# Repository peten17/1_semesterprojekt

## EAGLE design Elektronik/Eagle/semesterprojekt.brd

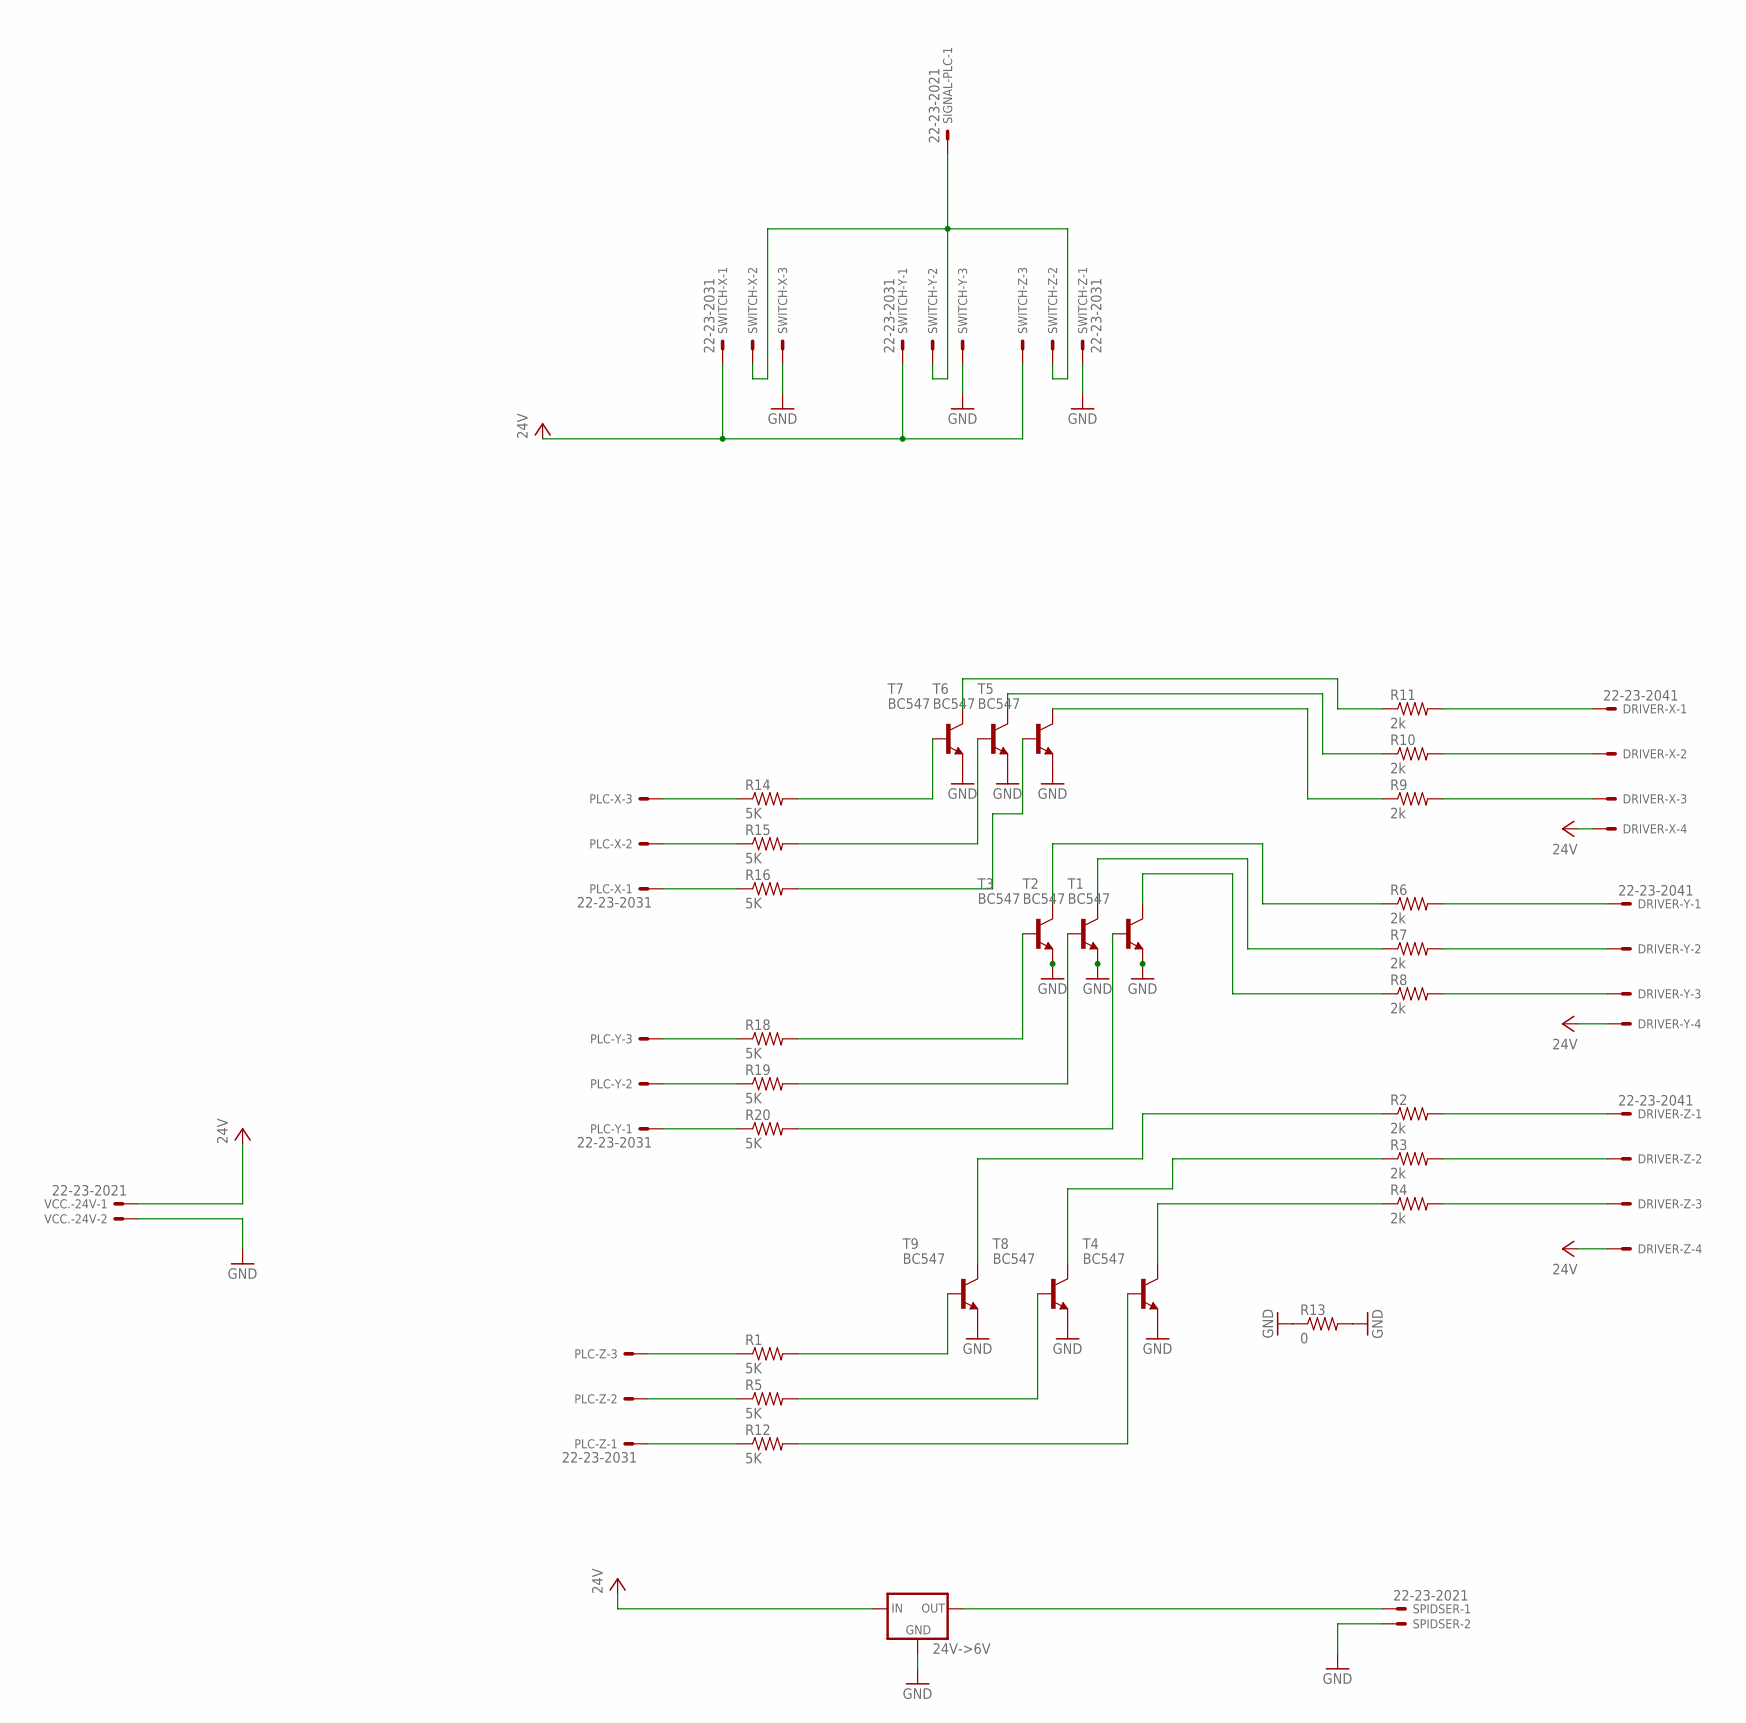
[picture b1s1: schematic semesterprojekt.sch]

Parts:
24V->6V: 78XXS
DRIVER-X: 22-23-2041
DRIVER-Y: 22-23-2041
DRIVER-Z: 22-23-2041
PLC-X: 22-23-2031
PLC-Y: 22-23-2031
PLC-Z: 22-23-2031
R1, R5, R12, R14, R15, R16, R18, R19, R20: 5K; 0204/7
R2, R3, R4, R6, R7, R8, R9, R10, R11: 2k; 0204/7
R13: 0; 0204/7
SIGNAL-PLC: 22-23-2021
SPIDSER: 22-23-2021
SWITCH-X: 22-23-2031
SWITCH-Y: 22-23-2031
SWITCH-Z: 22-23-2031
T1, T2, T3, T4, T5, T6, T7, T8, T9: BC547; TO92
VCC.-24V: 22-23-2021

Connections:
GND: 24V->6V.GND, R13.1, R13.2, SPIDSER.2, SWITCH-X.3, SWITCH-Y.3, SWITCH-Z.1, T1.3 (E), T2.3 (E), T3.3 (E), T4.3 (E), T5.3 (E), T6.3 (E), T7.3 (E), T8.3 (E), T9.3 (E), VCC.-24V.2
unnamed: DRIVER-Z.1, R2.2
unnamed: DRIVER-Z.2, R3.2
unnamed: DRIVER-Z.3, R4.2
unnamed: 24V->6V.OUT, SPIDSER.1
unnamed: R14.2, T7.2 (B)
unnamed: R15.2, T6.2 (B)
unnamed: R16.2, T5.2 (B)
unnamed: PLC-X.2, R15.1
unnamed: R18.2, T3.2 (B)
unnamed: R19.2, T2.2 (B)
unnamed: R20.2, T1.2 (B)
unnamed: R4.1, T4.1 (C)
unnamed: PLC-X.1, R16.1
unnamed: SIGNAL-PLC.1, SWITCH-X.2, SWITCH-Y.2, SWITCH-Z.2
unnamed: PLC-Y.3, R18.1
unnamed: R8.1, T1.1 (C)
unnamed: DRIVER-Y.3, R8.2
unnamed: R7.1, T2.1 (C)
unnamed: DRIVER-Y.2, R7.2
unnamed: R6.1, T3.1 (C)
unnamed: DRIVER-Y.1, R6.2
unnamed: PLC-Y.2, R19.1
unnamed: R9.1, T5.1 (C)
unnamed: DRIVER-X.2, R10.2
unnamed: R10.1, T6.1 (C)
unnamed: R11.1, T7.1 (C)
unnamed: PLC-Y.1, R20.1
unnamed: R3.1, T8.1 (C)
unnamed: DRIVER-X.1, R11.2
unnamed: DRIVER-X.3, R9.2
unnamed: R2.1, T9.1 (C)
unnamed: PLC-Z.1, R12.1
unnamed: PLC-Z.2, R5.1
unnamed: PLC-Z.3, R1.1
unnamed: PLC-X.3, R14.1
unnamed: R12.2, T4.2 (B)
unnamed: R5.2, T8.2 (B)
unnamed: R1.2, T9.2 (B)
VCC: 24V->6V.IN, DRIVER-X.4, DRIVER-Y.4, DRIVER-Z.4, SWITCH-X.1, SWITCH-Y.1, SWITCH-Z.3, VCC.-24V.1

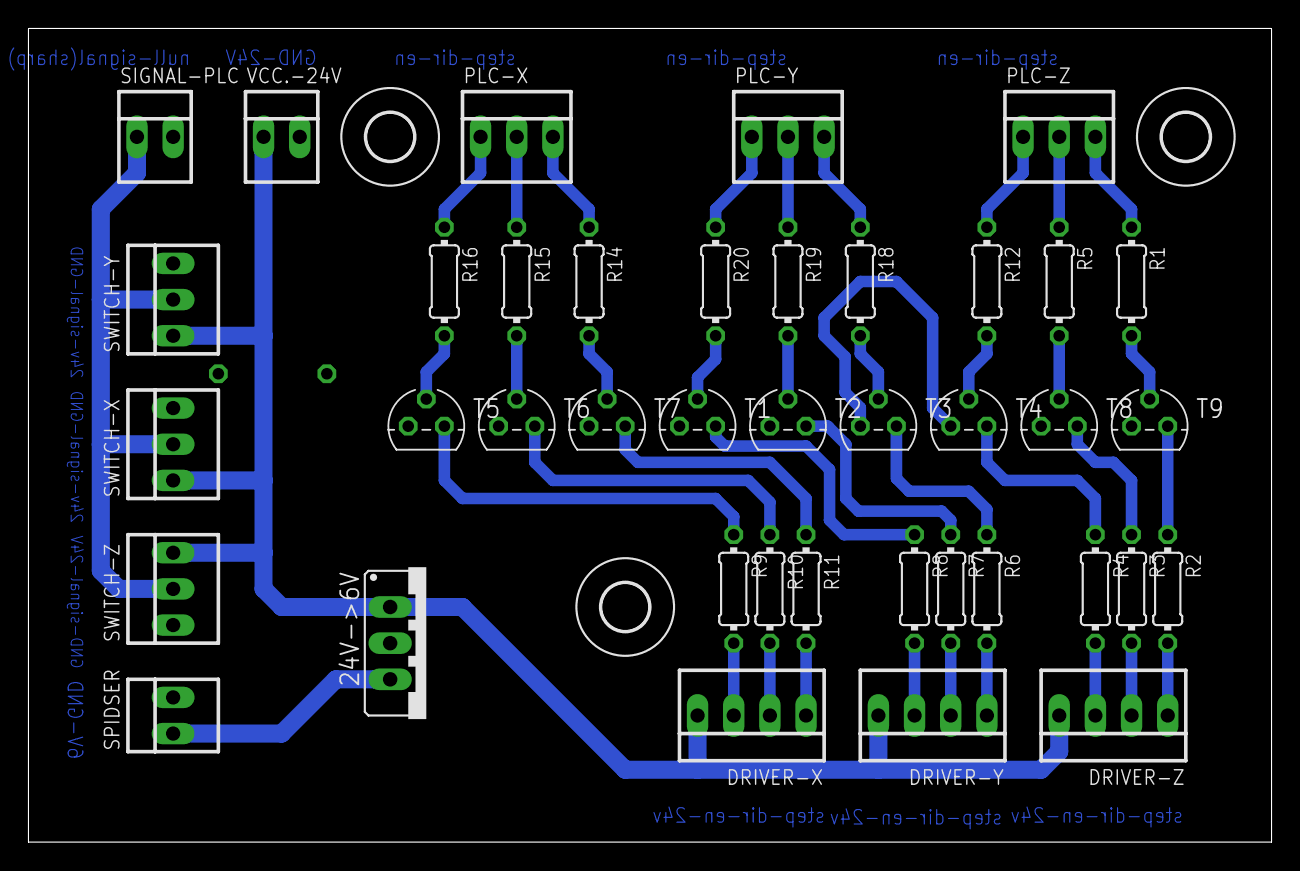
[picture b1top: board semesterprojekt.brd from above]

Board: 2 copper layers, 87.3 x 57.1 mm, 44 parts (1 on the bottom side), 40 nets.

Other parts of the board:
U$1, U$2, U$3: 3,3

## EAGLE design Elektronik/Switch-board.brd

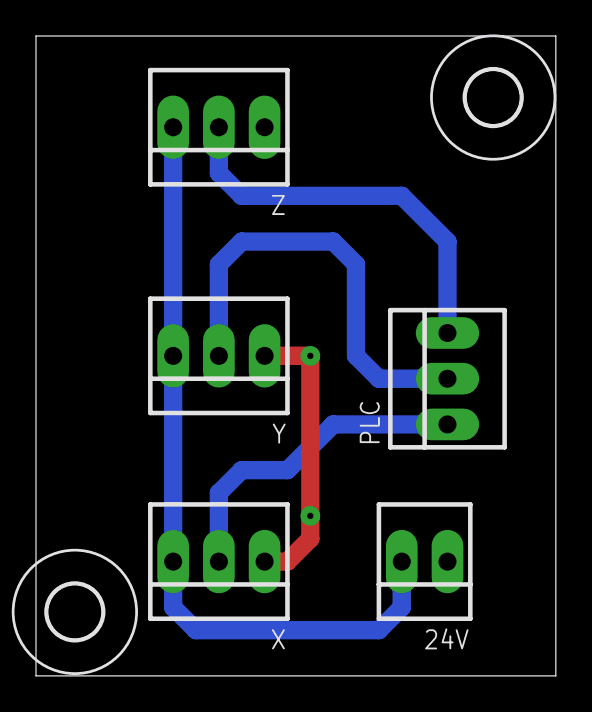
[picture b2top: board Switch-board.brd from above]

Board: 2 copper layers, 28.9 x 35.5 mm, 7 parts (0 on the bottom side), 5 nets.

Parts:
24V: 22-23-2021
PLC: 22-23-2031
U$1, U$2: 3,0
X: 22-23-2031
Y: 22-23-2031
Z: 22-23-2031

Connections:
GND: 24V.1, X.1, Y.1, Z.1
unnamed: PLC.1, X.2
unnamed: PLC.2, Y.2
unnamed: PLC.3, Z.2
VCC: 24V.2, X.3, Y.3, Z.3

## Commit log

2017-10-12 Reupload
2017-10-23 Sidehoved i gruppekontrakt
2017-10-23 Oprettelse af diverse dokumenter med rigtig skrift
2017-10-24 Tilføjelse af regler
2017-10-24 Flere regler
2017-10-24 jeg har tilføjet github til værktøjs sektionen
2017-10-30 Arbejdsfordeling
2017-10-30 Scannet gruppekontrakt(Underskrevet)
2017-10-30 Tidsplan tilføjet
2017-10-30 Ændring
2017-10-30 Efter vejledermøde
2017-11-01 første udkast af plc styring
2017-11-01 hurtig ændring i mappe orden
2017-11-01 v002
2017-11-01 test
2017-11-01 fjernede st
2017-11-02 Eagle tegning af board
2017-11-02 gen oploade
2017-11-02 Board sketch
2017-11-02 Småændringer i eagle
2017-11-06 kalibrering i st
2017-11-06 Elektronik Setup
2017-11-06 Her er java, før OOP optimering
2017-11-06 kredsløb
2017-11-06 kredsløb2
2017-11-06 Nu med Kredsløb
2017-11-06 kredsløb3
2017-11-06 Added første af to logbøger fra denne uge
2017-11-06 Med kredsløb
2017-11-06 Boardv2
2017-11-06 Update af de forskellige picture filer
    Stor updatering af OOP convertering.
2017-11-06 Comment
2017-11-06 Rettelser
2017-11-06 kalibrering fixet
2017-11-06 punktum
2017-11-06 redigering
2017-11-06 hurtig log
2017-11-06 backup moved
2017-11-06 Småændringer
2017-11-06 åben bart er der sket nogle ændringer siden jeg gemte den sidst såååå
2017-11-07 Logbog fra gårsdagens elektronik
2017-11-07 forløbig main
2017-11-07 boardv4
2017-11-07 Boardv3
2017-11-07 Logbog 2.
    tilføjet kilder
2017-11-07 Code is in OOP mode
2017-11-08 Logbog for i dag
2017-11-09 halv implementering af blyantspidseren
2017-11-09 færdig mangler bare test af implementering
2017-11-09 skrevet llogbog for de sidste par dage
2017-11-09 Skrev hvad vi herfra skal få lavet
2017-11-13 Driver board pdf
2017-11-13 PCB-2
2017-11-13 cycle tiden er rigtig nu og portende er sat rigtigt
2017-11-13 Visu
2017-11-13 problemformulering
2017-11-13 Interface
2017-11-13 Uploadet logbog samt java semesterprojekt
2017-11-13 Oprettet mappe
2017-11-13 Oprettet mappe i logbøger
2017-11-13 Logbog update
2017-11-14 shit
2017-11-15 interface2.0
2017-11-15 Jeg har skrevet logbog for i dag og lavet gevaldigt om på koden i java
    For beskrivelse se logbogen XD
2017-11-16 Ændring af enab
2017-11-17 Step
2017-11-18 Testside i AS
2017-11-20 Motor kører
2017-11-21 enkelte ændringer
2017-11-21 vi prøver igen
2017-11-21 :+1:
2017-11-26 Ændret meget få ting
    blablabla
2017-11-27 Lidt tekst ændring
2017-11-27 fejlsøning
2017-11-27 Start på indledning
2017-11-27 Kalibrering af robot
2017-11-27 Merge
2017-11-27 Rettet så der kan scales, men der er små problemer med den message der skal sendes
2017-11-27 ændringer i reset
2017-11-27 Eagle
2017-11-27 All dat crazy shit!
2017-11-28 percentage virker
2017-11-30 småting
2017-11-30 Vi har en firkant! Der ikke er skæv
2017-12-01 Har lavet en beta af auto-scaling
    Har også lavet en backup, hvilket jeg tror også ryger med op her
2017-12-02 Java Rapport
2017-12-02 Små ændringer
2017-12-02 Image klassens beskrivelse er begyndt og en alpha er færdig XD
2017-12-04 elektronik
2017-12-04 lidt rapport og connection delen af koden er klar
2017-12-04 rettelser i connect
2017-12-04 Det virker ikke
2017-12-04 version 002
2017-12-04 Setup ændringer + lidt tekst
2017-12-04 Små ting
2017-12-04 v2 is online
2017-12-04 driver
2017-12-04 v003
2017-12-04 v003 is online
2017-12-05 java short code
2017-12-05 test og forbedringer
2017-12-05 test.png
2017-12-05 kode ændringer til testaf maximum billede
2017-12-05 Ændringer
2017-12-05 placering af spidser
2017-12-05 plz virk
2017-12-05 Lille update
2017-12-05 ændringer fastver og main
2017-12-05 her mads
2017-12-06 fin justering mm.
2017-12-06 The real deal
2017-12-06 en linjes ænding i message og constroctor ænding i massage og partimage
2017-12-06 Elektronik og start på komplet kredsløb
2017-12-06 ST doku
2017-12-06 Komplet interface af elektronik opsætning
2017-12-06 Forced push
2017-12-07 Elektronik, skrivning
2017-12-07 elektronik rettelse
2017-12-07 Elektronik rettelser
2017-12-07 kodedannings ændring så den er simplere og bedre
2017-12-07 Oprettelse af version 5
2017-12-07 mona
2017-12-08 dsaf
2017-12-08 Ændring af varable
2017-12-08 v005
2017-12-11 Tilføjelse af sidste program
2017-12-11 omstukturering af raport del st
2017-12-11 endelig st
2017-12-12 JavaDone
2017-12-12 Resume
2017-12-12 resultater
2017-12-12 Konklusion
2017-12-12 henvisningerJava
2017-12-13 rapport
2017-12-13 TCP-kort beskrivelse
2017-12-13 Rapport endelig
2017-12-13 bilag
2017-12-13 mappe struktur
2017-12-13 Rapport + pdf
2017-12-14 variabler er ændret
2017-12-14 java ændringer og bilag eksport
2017-12-14 Endelig rapport!
2017-12-14 Timelapse
2017-12-14 Rapport med underskrift
2017-12-14 Aflevering
2018-01-16 samling i nu mappe
